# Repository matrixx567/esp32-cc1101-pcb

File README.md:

# esp32-cc1101-pcb

## Used Libraries

https://github.com/r0oland/ESP32_mini_KiCad_Library
https://github.com/cyrozap/KiCad.git

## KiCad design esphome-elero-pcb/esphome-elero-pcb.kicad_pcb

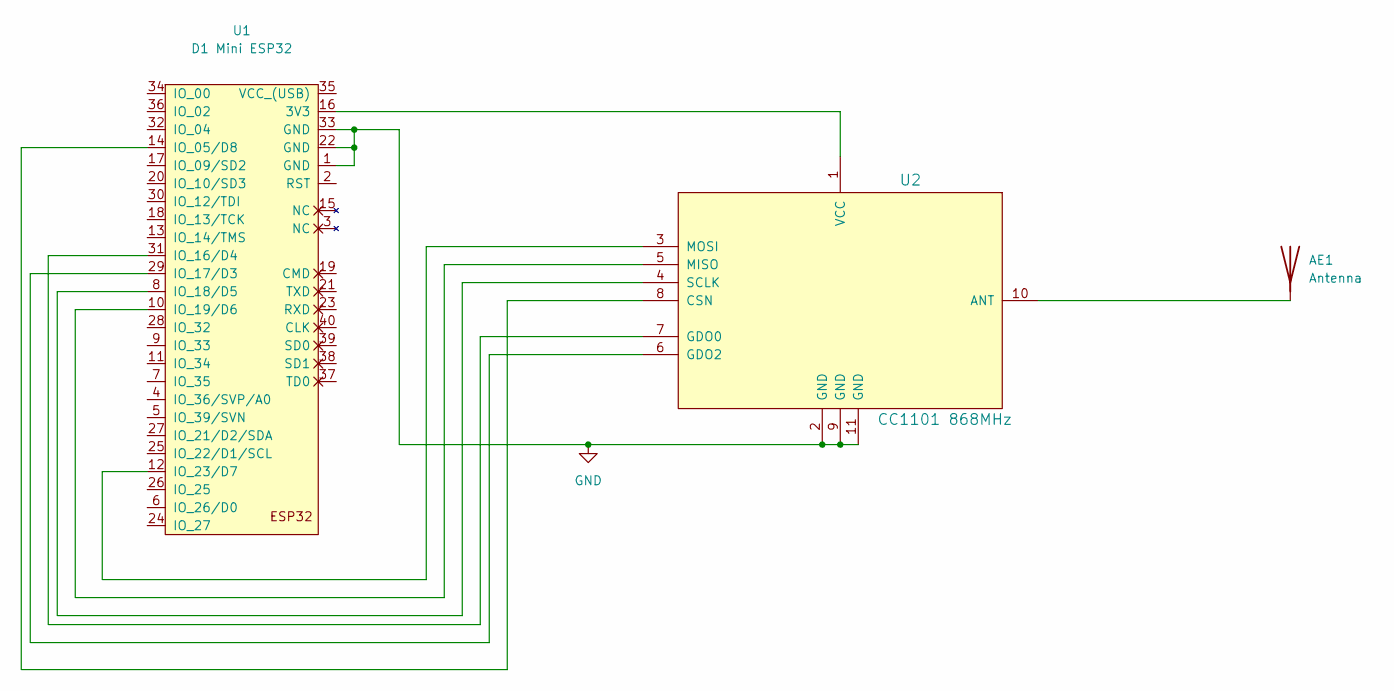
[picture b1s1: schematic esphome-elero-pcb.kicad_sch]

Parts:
AE1: Antenna; TestPoint_Loop_D1.80mm_Drill1.0mm_Beaded
U1: D1 Mini ESP32; ESP32_mini
U2: CC1101 868MHz; CC1101-868MHz-Module

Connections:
GND: U1.1 (GND), U1.22 (GND), U1.33 (GND), U2.2 (GND), U2.9 (GND), U2.11 (GND)
unnamed: AE1.1 (A), U2.10 (ANT)
unnamed: U1.16 (3V3), U2.1 (VCC)
unnamed: U1.14 (IO_05/D8), U2.8 (CSN)
unnamed: U1.31 (IO_16/D4), U2.7 (GDO0)
unnamed: U1.29 (IO_17/D3), U2.6 (GDO2)
unnamed: U1.8 (IO_18/D5), U2.4 (SCLK)
unnamed: U1.10 (IO_19/D6), U2.5 (MISO)
unnamed: U1.12 (IO_23/D7), U2.3 (MOSI)

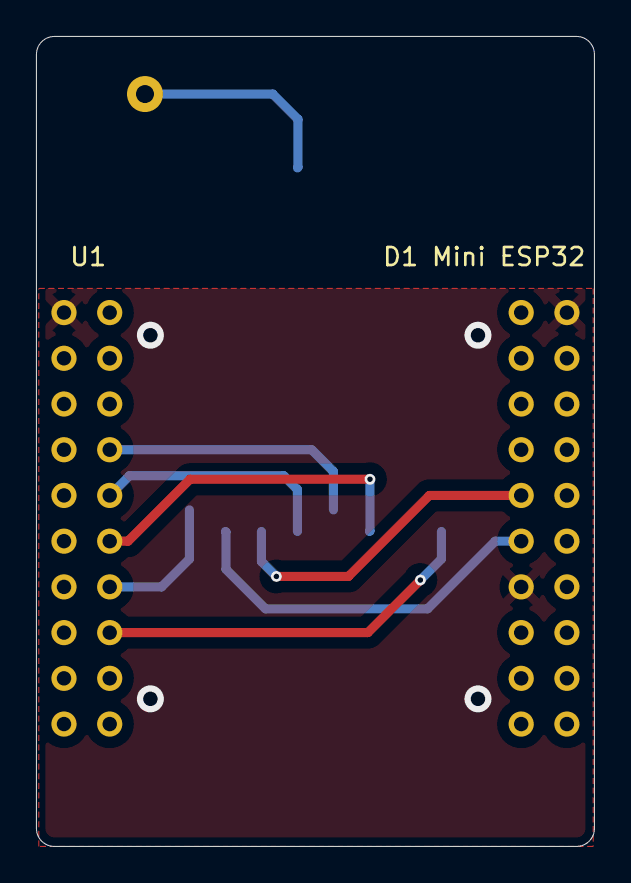
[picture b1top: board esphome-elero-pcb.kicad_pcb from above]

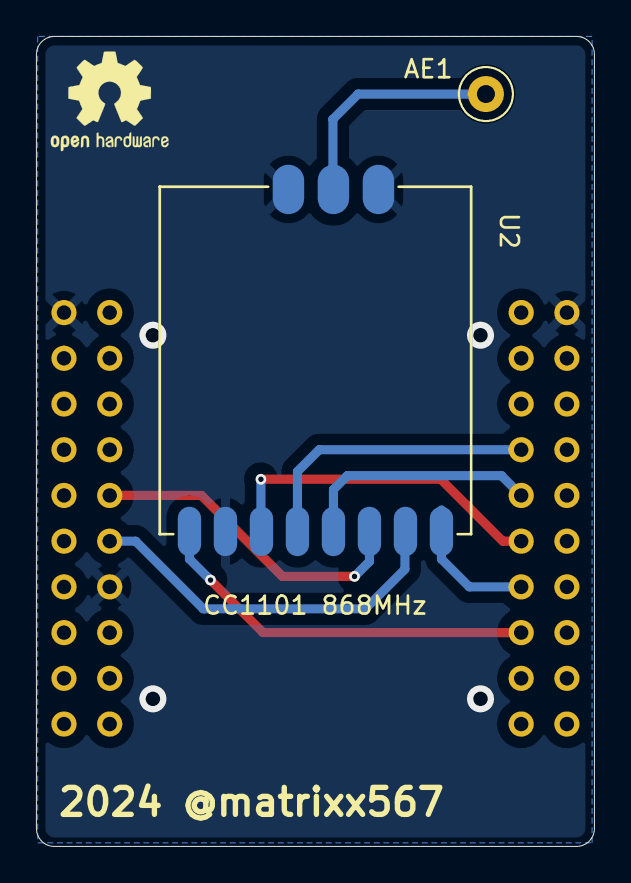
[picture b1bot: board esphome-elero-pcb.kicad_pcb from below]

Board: 2 copper layers, 31.0 x 45.0 mm, 3 parts (2 on the bottom side), 9 nets.

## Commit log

2024-03-16 Initial commit.
2024-03-17 First production version.
